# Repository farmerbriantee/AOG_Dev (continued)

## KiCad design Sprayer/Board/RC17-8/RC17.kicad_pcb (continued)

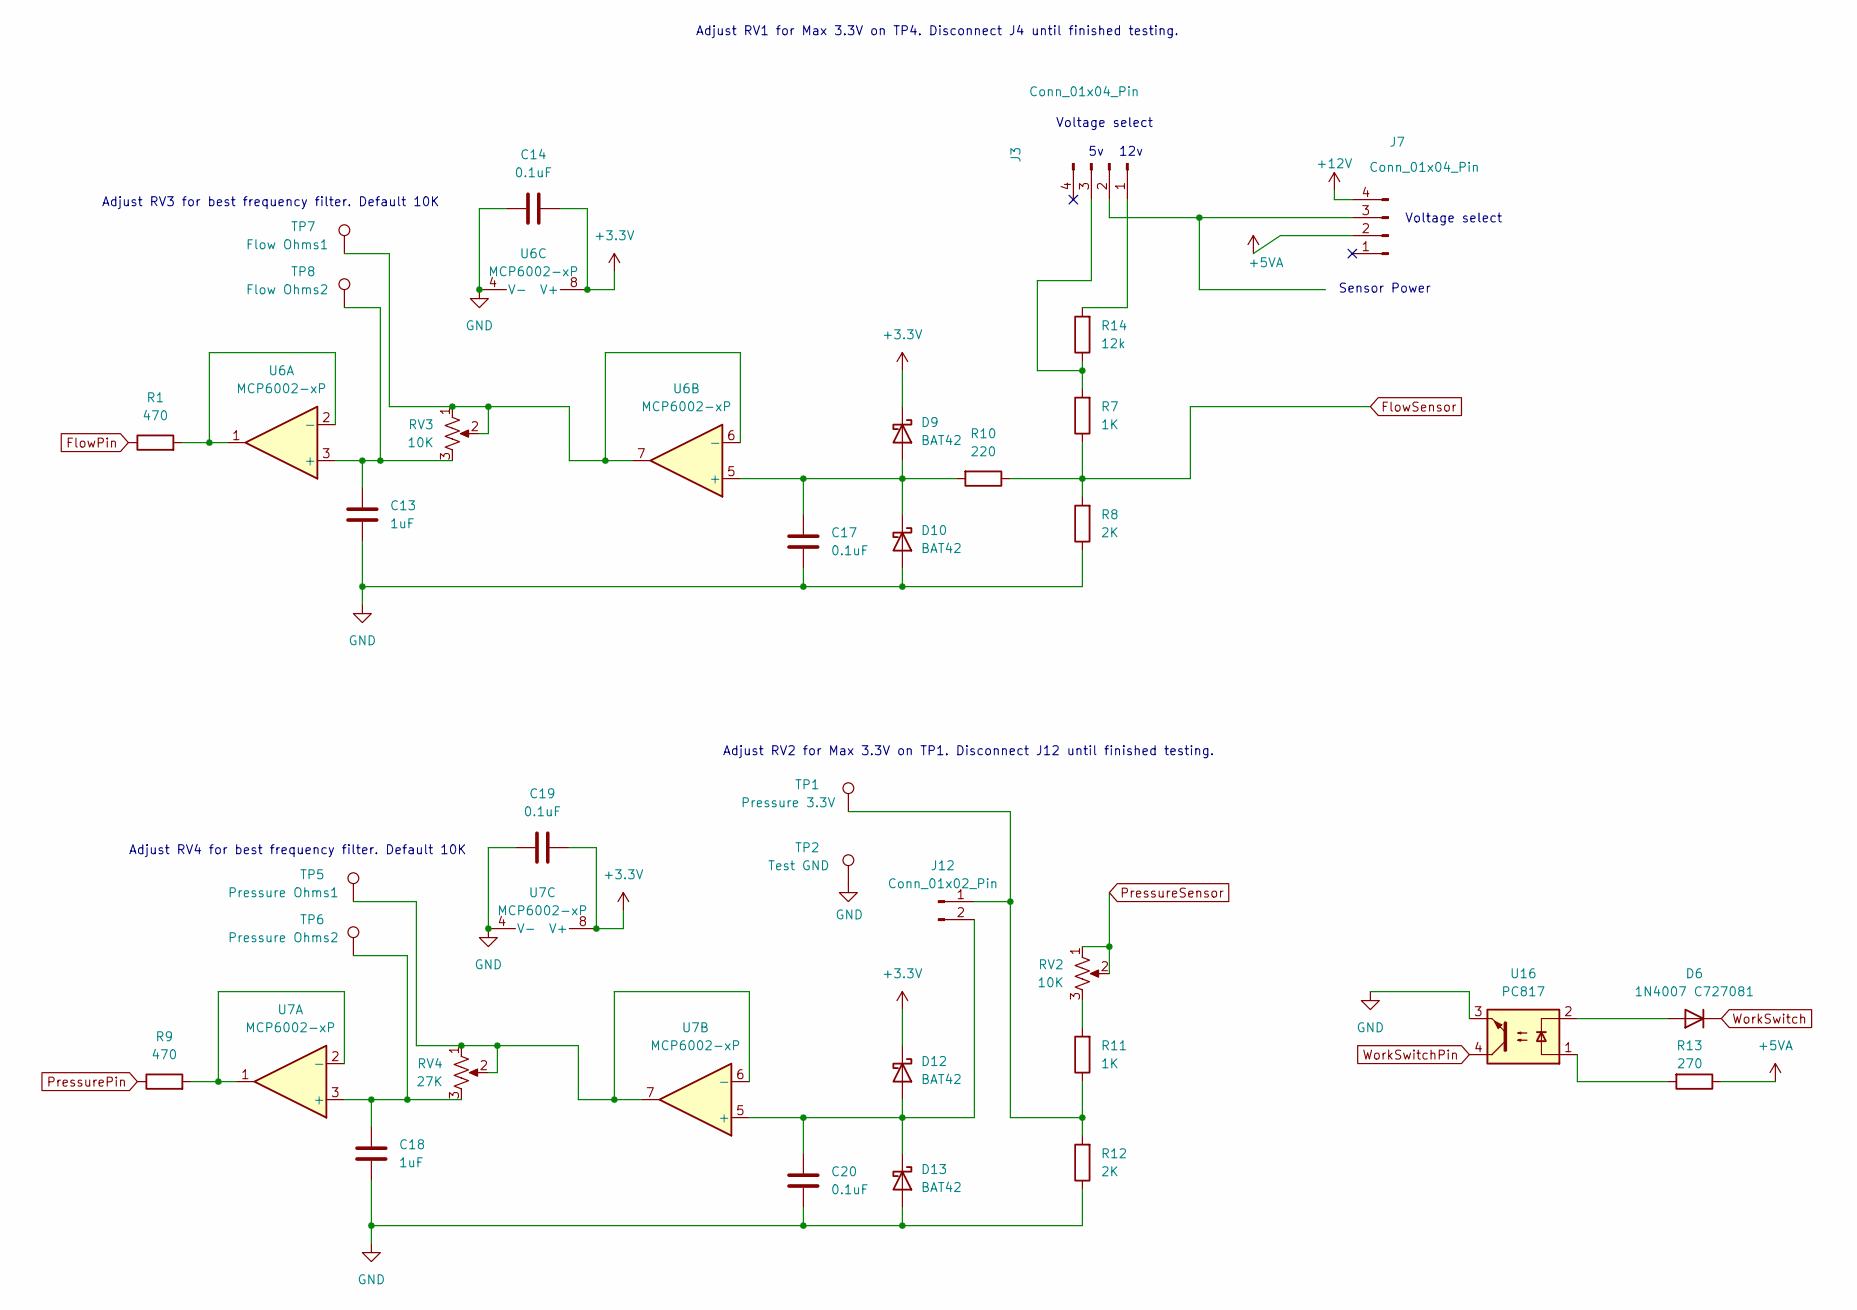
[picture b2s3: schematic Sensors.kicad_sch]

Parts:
C13, C18: 1uF; C_0805_2012Metric
C14, C17, C19, C20: 0.1uF; C_0603_1608Metric
D6: 1N4007 C727081; SMA(DO-214AC)
D9, D10, D12, D13: BAT42; D_SOD-123
J3, J7: Conn_01x04_Pin; PinHeader_1x04_P2.54mm_Vertical
J12: Conn_01x02_Pin; PinHeader_1x02_P2.54mm_Vertical
R1, R9: 470; C_0603_1608Metric
R7, R11: 1K; R_0603_1608Metric
R8, R12: 2K; R_0603_1608Metric
R10: 220; R_0603_1608Metric
R13: 270; R_0603_1608Metric
R14: 12k; R_0603_1608Metric
RV2, RV3: 10K; Potentiometer
RV4: 27K; Potentiometer
TP1: Pressure 3.3V; TestPoint_THTPad_D2.5mm_Drill1.2mm
TP2: Test GND; TestPoint_THTPad_D2.5mm_Drill1.2mm
TP5: Pressure Ohms1; TestPoint_THTPad_D2.5mm_Drill1.2mm
TP6: Pressure Ohms2; TestPoint_THTPad_D2.5mm_Drill1.2mm
TP7: Flow Ohms1; TestPoint_THTPad_D2.5mm_Drill1.2mm
TP8: Flow Ohms2; TestPoint_THTPad_D2.5mm_Drill1.2mm
U6, U7: MCP6002-xP; SOIC127P600X175-8N
U16: PC817; SMD-4_4.6x7.62mm_P2.54mm

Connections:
+3.3V: C14.2, C19.2, D9.1 (K), D12.1 (K), U6.8 (V+), U7.8 (V+); also elsewhere on the board
+5VA: J3.4, J7.2, R13.1; also elsewhere on the board
FlowPin: R1.1; also elsewhere on the board
FlowSensor: J3.2, J7.3; also elsewhere on the board
GND: C13.2, C14.1, C17.2, C18.2, C19.1, C20.2, D10.2 (A), D13.2 (A), R8.1, R12.1, TP2.1, U6.4 (V-), U7.4 (V-), U16.3; also elsewhere on the board
unnamed: D6.2 (A), U16.2
unnamed 16: C17.1, D9.2 (A), D10.1 (K), R10.2, U6.5 (+); also elsewhere on the board
unnamed: C20.1, D12.2 (A), D13.1 (K), J12.2, U7.5 (+)
unnamed 21: J3.1, R7.1, R8.2, R10.1, R14.2; also elsewhere on the board
unnamed: J12.1, R11.1, R12.2, TP1.1
unnamed: R11.2, RV2.3
unnamed: R13.2, U16.1
unnamed: C13.1, RV3.3, TP8.1, U6.3 (+)
unnamed: R1.2, U6.1, U6.2 (-)
unnamed: RV3.1, RV3.2, TP7.1, U6.6 (-), U6.7
unnamed: C18.1, RV4.3, TP6.1, U7.3 (+)
unnamed: R9.2, U7.1, U7.2 (-)
unnamed: RV4.1, RV4.2, TP5.1, U7.6 (-), U7.7
PressurePin: R9.1; also elsewhere on the board
PressureSensor: RV2.1, RV2.2; also elsewhere on the board
WorkSwitch: D6.1 (K); also elsewhere on the board
WorkSwitchPin: U16.4; also elsewhere on the board

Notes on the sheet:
Voltage select
12v
Adjust RV1 for Max 3.3V on TP4. Disconnect J4 until finished testing.
Adjust RV3 for best frequency filter. Default 10K
Adjust RV2 for Max 3.3V on TP1. Disconnect J12 until finished testing.
Sensor Power
Adjust RV4 for best frequency filter. Default 10K

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
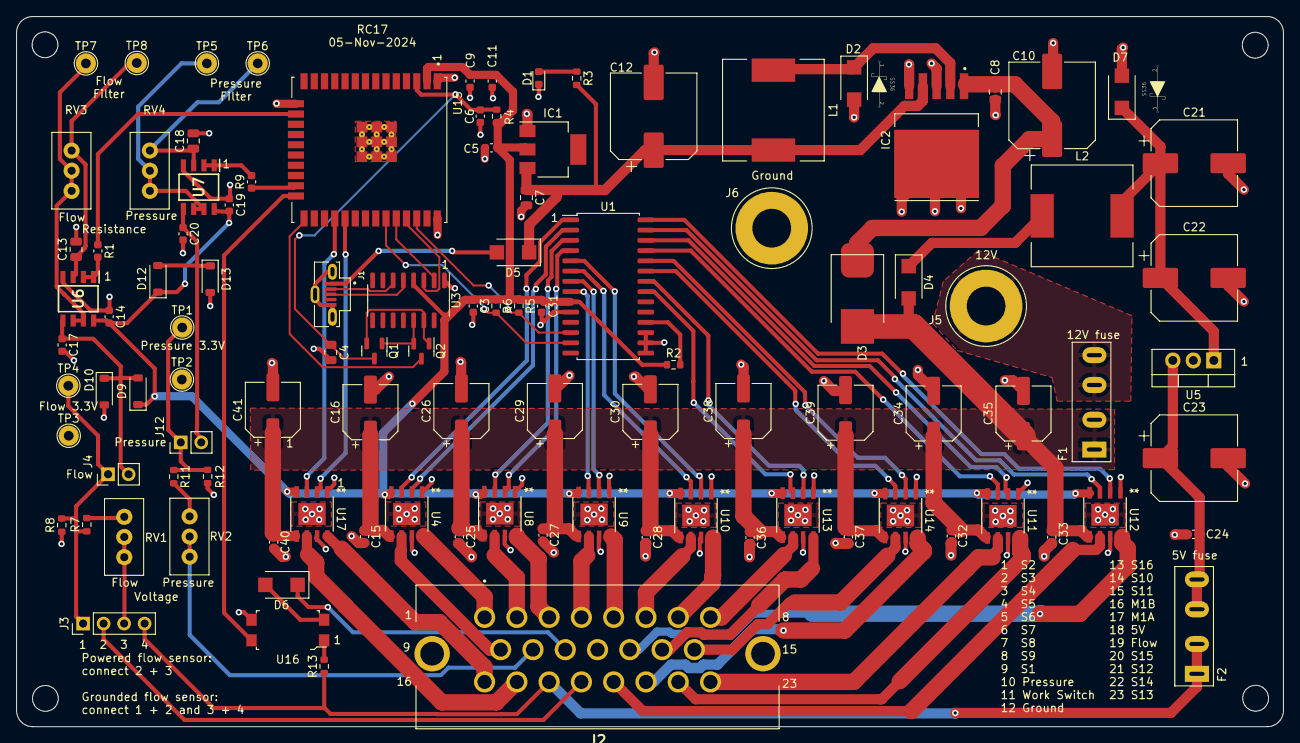
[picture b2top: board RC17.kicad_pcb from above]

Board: 2 copper layers, 157.0 x 88.0 mm, 111 parts (0 on the bottom side), 81 nets.

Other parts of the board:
 : MountingHole_3.2mm_M3
 #2,  #6: SS36 descriptor
 #3,  #4,  #5: MountingHole_3.2mm_M3
J4: Conn_01x02_Pin; PinHeader_1x02_P2.54mm_Vertical
RV1: 10K; Potentiometer
TP3: Test GND; TestPoint_THTPad_D2.5mm_Drill1.2mm
TP4: Flow 3.3V; TestPoint_THTPad_D2.5mm_Drill1.2mm

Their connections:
GND: TP3.1; also elsewhere on the board
unnamed 16: J4.2; also elsewhere on the board
unnamed 21: J4.1, TP4.1; also elsewhere on the board

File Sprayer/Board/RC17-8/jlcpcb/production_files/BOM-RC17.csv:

Comment,Designator,Footprint,LCSC
27K,RV4,Potentiometer,C118932
10K,"RV1,RV2,RV3",Potentiometer,C118954
0.1uF,"C14,C15,C17,C19,C20,C24,C25,C27,C28,C3,C31,C32,C33,C36,C37,C40,C6,C9",C_0603_1608Metric,C14663
10uF,C7,C_0805_2012Metric,C15850
S10MC,D3,D_SMC_larger_pads,C169472
500,R3,R_0603_1608Metric,C22808
270,R13,R_0603_1608Metric,C22966
2K,"R12,R8",R_0603_1608Metric,C22975
470,"R1,R9",C_0603_1608Metric,C23179
BSS138,"Q1,Q2",SOT-23,C255592
10K,"R2,R4",R_0603_1608Metric,C25804
Conn_01x04_Pin,J3,PinHeader_1x04_P2.54mm_Vertical,C2691448
1uF,"C13,C18,C4,C8",C_0805_2012Metric,C28323
47uF,"C16,C26,C29,C30,C34,C35,C38,C39,C41",CP_Elec_6.3x5.4,C2836440
SS36,"D2,D7",SMA(DO-214AC),C2903825
1K,"R11,R7",R_0603_1608Metric,C2907113
330uF,C12,CP_Elec_10x10.5,C3032175
470uF,"C10,C21,C22,C23",CP_Elec_10x10.5,C310845
776087-1-776087-1,J2,7760871,C378893
2.2K,"R5,R6",R_0603_1608Metric,C4190
MCP23017_SO,U1,SOIC-28W_7.5x17.9mm_P1.27mm,C47023
Conn_01x02_Pin,"J12,J4",PinHeader_1x02_P2.54mm_Vertical,C492401
C492610,"F1,F2",Fuse_Holder_C492610,C492610
DRV8251,"U10,U11,U12,U13,U14,U17,U4,U8,U9",DRV8251ADDR,C5218844
LM7805_TO220,U5,TO-220-3_Vertical,C5444281
BAT42,"D10,D12,D13,D9",D_SOD-123,C5805639
105133-0011,J1,MOLEX_105133-0011,C586226
22uF,"C11,C5",C_0603_1608Metric,C59461
PC817,U16,SMD-4_4.6x7.62mm_P2.54mm,C66405
ESP32-WROOM-32U,U15,XCVR_ESP32-WROOM-32U,C701344
1N4007   C727081,"D4,D5,D6",SMA(DO-214AC),C727081
MCP6002-xP,"U6,U7",SOIC127P600X175-8N,C7377
XL2596,IC2,TO263-5L,C74190
LED,D1,LED_0603_1608Metric,C84263
CH340C,U3,SOIC-16_3.9x9.9mm_P1.27mm,C84681
AZ1117,IC1,SOT-223,C92102
SMDRI127-330MT,"L1,L2",TMPA1265SP-101MN-D,C9400
Test GND,TP3,TestPoint_THTPad_D2.5mm_Drill1.2mm,
Pressure Ohms2,TP6,TestPoint_THTPad_D2.5mm_Drill1.2mm,
12V ,J5,PowerPin,
Flow Ohms2,TP8,TestPoint_THTPad_D2.5mm_Drill1.2mm,
Flow Ohms1,TP7,TestPoint_THTPad_D2.5mm_Drill1.2mm,
Pressure Ohms1,TP5,TestPoint_THTPad_D2.5mm_Drill1.2mm,
Ground,J6,PowerPin,
Pressure 3.3V,TP1,TestPoint_THTPad_D2.5mm_Drill1.2mm,
Test GND,TP2,TestPoint_THTPad_D2.5mm_Drill1.2mm,
Flow 3.3V,TP4,TestPoint_THTPad_D2.5mm_Drill1.2mm,

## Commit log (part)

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2025-02-10 Pivot heading averages
2025-02-10 Set ports to 18888, 19999. Clean up App.configs
2025-02-10 Start the jobs menu
2025-02-11 jobnew btn problem
2025-02-11 New and resume Job - basic working
2025-02-11 New and resume, multi resume for jobs
2025-02-12 Fix up Fields Form for Jobs
2025-02-12 Start double file picker
2025-02-12 Multi Open File Field and Job
2025-02-12 Circles of Pain from all the choices you can make opening and closing and resuming.
2025-02-13 Tracks to Tracklines naming oops in FormExisting
2025-02-13 Rearrange Field menu
2025-02-13 Wire up Delete btns on Field and Job picker
2025-02-13 File Picker - make functions for duplicate code
2025-02-13 ShowFields
2025-02-13 ListViewItemComparer
2025-02-13 moved ListViewItemSorter to ExtensionMethods
2025-02-13 moved patchList from CPatches to FormGPS
2025-02-14 ISOXML back on field menu
2025-02-14 Fix iso event call
2025-02-14 Clean up FormField
2025-02-14 list view sorter added to filePicker
2025-02-14 Sort added to OpenJob Picker
2025-02-14 Clean up FormFilePicker
2025-02-14 Field and Job open and new
2025-02-14 Remove job elements from KML, ISOXML andFix delete sections
2025-02-14 Jobs to open jb in picker
2025-02-15 File Validation JobNew Form
2025-02-15 oglZoom bleeding on menu
2025-02-15 Move compass
2025-02-15 FormFieldOpen Cleanup and disable buttons when no item is selected
2025-02-15 .editorConfig
2025-02-15 Field Start pos and name to opening
2025-02-16 Serbian added
2025-02-16 enable use Field once field is selected
2025-02-16 Contour button fix
2025-02-17 CSV Languages
2025-02-17 Language Keys and Values for FormGPS
2025-02-17 Language Menu change
2025-02-17 change GUI to ggStr
2025-02-17 clean up ResX
2025-02-17 gStr to ggStr for class L:ang
2025-02-18 xlsx import and language build
2025-02-18 Config Form culture labels
2025-02-18 Config and Steer label widths and translations
2025-02-18 FileSaveBoundary only when you actualy change something
2025-02-18 CalculateSectionPatchesMinMax already done in oglZoom_Paint
2025-02-18 remove csv and old xls
2025-02-18 bndSelect instead of 0
2025-02-18 tabUTurn_Leave only reset when changed
2025-02-18 remove csv from project
2025-02-19 Fix culture in BndTool
2025-02-19 Clean up translation.xls
2025-02-23 removed AppData settings
2025-02-23 NumericUpDown cleanup2
2025-02-23 NumericUpDown cleanup3
2025-02-23 double values
2025-02-24 static unit conversion
2025-02-24 use static units
2025-02-24 use mode inside NumericUpDown
2025-02-24 Font based on height
2025-02-24 fix nudZone's
2025-02-27 CNMEA cleanup
2025-02-27 Update AgIO to dual
2025-02-27 fix numeric font size
2025-02-27 Finalize comms between tool and gps, Scan and Hello
2025-02-28 remove isMetric
2025-02-28 distanceFromCurrentLine in meters
2025-02-28 distanceFromCurrentLine in meters2
2025-02-28 rename agone to AgIO
2025-02-28 Sort Settings
2025-03-01 use pivotAxlePos instead of fix
2025-03-01 cleanup fix-fix calculation (needs testing in field)
2025-03-01 button should work when revers is off
2025-03-01 Revert "Fix Antenna dots"
    This reverts commit 76b627b59456f8a2280241dca5fc5241301b7237.
2025-03-01 toolpos for oglBack not pivot
2025-03-02 larger bounding box for section culling
2025-03-02 changed sim so its rotation around a center
2025-03-02 FileOpenField cleanup
2025-03-02 removed unnecessary SetZoom calls
2025-03-02 cleanup variables
2025-03-02 simplify PanelsAndOGLSize & CheckColorFor255
2025-03-02 Contour and YouTurn steerangle calculations to guidance class
2025-03-03 Separate Vehicle, Tool & Interface
2025-03-03 Save & load for ToolSettings
2025-03-03 set lat&lon on sim reset
2025-03-03 RepeatButton
2025-03-03 removed References
2025-03-03 fix Settings
2025-03-03 automatic changed designer code
2025-03-03 interface to user
2025-03-03 Config form to vehicle/tool outline
2025-03-03 Resort and Rename settings
2025-03-03 Rename User settings moved from vehicle
2025-03-03 Endless renaming sheesh
2025-03-04 Remove display settings to variable doubling
2025-03-04 And more settings to props removed
2025-03-04 cleanup customColors & buttonOrder & swapDayNight
2025-03-04 FormConfig cleanup and fix tab Enter/Leave
2025-03-04 use settings directly
2025-03-04 use settings directly less reloading of all settings
2025-03-04 Settings Save to Profile. Not quite there
2025-03-04 Fix Save and Load
2025-03-04 Sort and group AgIO settings
2025-03-05 serial double settings
2025-03-05 Clean up settings, final double deletes
2025-03-05 Cam Pitch and Zoom doubles
2025-03-05 double settings
2025-03-05 Tool Setting duplicates
2025-03-05 opengl -> lost and isFirstHeadingSet move to Ortho drawing
2025-03-05 simplify btnSection and btnZone buttons
2025-03-06 fix zone button
2025-03-06 Youturn
2025-03-07 PerformClick to function call for autosteer and youturn
2025-03-07 more room for youTurnPhases
2025-03-07 GPS Out Class
2025-03-07 wrong branch, oops
2025-03-08 GPSOut settings
2025-03-08 Fix up main gui
2025-03-08 Traffic to GPSOut controls red green for button
2025-03-09 Writeline to Write
2025-03-09 Graphics and positioning for Win 11 and win 10
2025-03-09 proper byte counting
2025-03-09 Fix keyboard from sizing
2025-03-10 Add labels for load save new
2025-03-10 BackgroundWorker with skip send if still sending
2025-03-10 Remove awkward rtcm messages
2025-03-10 survive buffer overflow
2025-03-11 Fixed Distance Lookahead
2025-03-11 fix sim reverse
2025-03-11 sim heading after reset
2025-03-12 lengthen Track if close to ends
2025-03-12 fix Uturn gets longer too
2025-03-12 time based
2025-03-12 Vehicle/Tool loading and saving made easier, updates labels. Remove Ask on Load. No close after loading vehicle
2025-03-13 Add GSA and ZDA to GPSOut
2025-03-13 catch e removed
2025-03-14 Set nuds to Small
2025-03-15 Redo summary page of config
2025-03-15 Convert To AOG
2025-03-15 update ignore
2025-03-15 AgOpenGPS -> AOG
2025-03-16 First Screen, Remove any Default XML files or saving
2025-03-16 update labels functions
2025-03-17 PGN233 Tool Data fixed
2025-03-18 Dubins removed, Nozzle and section build added, Nud formatting fixed
2025-03-18 Fix up nozz display panel
2025-03-18 Modsim btn to run from AgIO
2025-03-18 reset U-turn when guidance line changes
2025-03-18 new vec2 from vec3
2025-03-19 local values
2025-03-19 if enabled it turns off U-turn when line changes
2025-03-19 fix track loading & U-turn
2025-03-24 Change settings and field icons to look different
2025-03-27 TM171 code added
2025-03-27 update spray board
2025-03-29 Refactor duplicate functions into extension methods
2025-04-01 untouched v4.1 firmware
2025-04-01 reset v4.1 firmware
2025-04-01 Add changes
2025-04-02 board gerber
2025-04-03 Clean up and speed up 4.1 firmware
2025-04-03 while back to if
2025-04-05 ToolSteer Firmware made
2025-04-05 Clean up files and dirs
2025-04-06 Add NanoSpray
2025-04-07 fix esp pid
2025-04-08 Spray ESP32 code fixes
2025-04-08 Nozzle config settings fixed
2025-04-08 local reference
2025-04-08 unnecessary track design Clear
2025-04-08 combined BuildTracks and QuickAB readonly List<CTrk>
2025-04-09 Add NozzESP
2025-04-09 Nozzle fixes
2025-04-10 Noz config Hz added
2025-04-10 126 to 226 for steer module
2025-04-10 Nozzle mods and Firmware update for limits
2025-04-10 uturn buttons visible more
2025-04-11 remove some files
2025-04-11 Change network for ESP
2025-04-11 Change network back to 1.1
2025-04-11 isSteer sent for pgn
2025-04-12 fixes in headache and handline forms
2025-04-12 Revert "uturn buttons visible more"
    This reverts commit 8490d8eeedc892067f2190cbf0d687ce638eec13.
2025-04-12 Antenna Height and Offset settings in steer form
2025-04-13 Add roll correction and Fix slide/steer roll effect
2025-04-13 toolDual hex
2025-04-13 Add tool antenna offset compensation.
2025-04-13 fix DrawPolygon for LineStrips
2025-04-14 AP Mode ESP32
2025-04-14 fix oglBack drawing and Section_Widths not loading correctly
2025-04-15 Currently being drawn patches to BBuffer
2025-04-15 update Nozzle labels
2025-04-15 Fix section width nuds
2025-04-15 fix ab line extension
2025-04-16 Minor refactoring, make the PGNs more readable
2025-04-17 fix offset u-turn & offset saving
2025-04-17 NozzNano Sln
2025-04-17 More data on Nozz config screen
2025-04-18 Clean up nozzle config
2025-04-19 Add IMU TM171 serial
2025-04-21 Metering and Flow selection, Kp added
2025-04-21 USe Pow for metering gain
2025-04-21 Arrange Nozzle Confiog
2025-04-21 Separate metering and Flow nuds
2025-04-22 Section Lights color correct for day night
2025-04-23 NozzESP Metering gain function simplify
2025-04-23 Invert roll - button did nothing. Add event.
2025-04-26 add metering to NozzNano
2025-04-27 toggle contour lock state on autosteerbtn press.
2025-04-27 Fix AgIO keyobard for culture
2025-04-27 roll tracking
2025-04-28 IMU set to 6 bytes for speed
2025-04-29 Add Edge Finding ABLine
2025-04-30 Fix the ISOXML
2025-05-01 add vtg back in
2025-05-01 Remove jump fix test thingy
2025-05-03 antenna offset to +-2m
2025-05-04 fix U-turn math problem
2025-05-04 Add back in gpsPts
2025-05-04 Allow send to serial and udp RTCM
2025-05-04 Allow udp and serial rtcm
2025-05-05 U-turn failed when a-b segment is created outside the boundary
2025-05-07 Remove smoothing.
2025-05-08 remove extra points in AB lines
2025-05-12 DebuggerDisplay
2025-05-12 U-turn use right segment
2025-05-13 Add Create heading for ABDraw
2025-05-13 Add heading to EdgeAB
2025-05-14 Try catch around DrawPolygon NozzNano updates
2025-05-14 Add GPS Correction line setting
2025-05-14 Fix the short line issue ABDraw
2025-05-14 vec3 to vec2
2025-05-14 cleanup vec3.cs
2025-05-15 removed Math.Round for defaultSectionWidth
2025-05-15 section array to list with max 256 sections
2025-05-15 Redo BndTool Gui
2025-05-17 cleanup some code
2025-05-17 isRemoteSectionControl
2025-05-17 imu and bnd Tool changes
2025-05-19 Create Tool Steer Settings
2025-05-20 Build tool steer form for settings
2025-05-20 Extend endpoints for AB Lines in ABDraw
2025-05-23 Init Classes and uploader
2025-05-23 Make FileSaveEverything Async
2025-05-23 Store as Polygon
2025-05-23 Add Images
2025-05-23 async task if for Closing AOG with AgShareUpload
2025-05-23 add Activate button formAgShareSettings
2025-05-23 Upload Methods added
2025-05-23 small fix when we close the field
2025-05-23 New Closing Method to match upload with AgShare
2025-05-25 fix resource.resx AgShare
2025-05-25 inconsistent AgShare settings
2025-05-25 Cleanup AgShare, add Linklabel, Keyboard link, PasteClipboardBtn
2025-05-25 Upload Outer and Innerboundaries
2025-05-25 clean
2025-05-25 fix missing flag and Add Innerboundaries to Upload Method for AgShare (#66)
    * set isAgShareUploader to false when done
    * Upload Outer and Innerboundaries
    * clean
2025-05-27 initial stuff for Downloader
2025-05-29 section lbl's to section count instead of zones
2025-05-29 use remoteSectionControl bool instead of settings
2025-05-29 AgShare Download options done
2025-06-07 better split in upload download
2025-06-08 Cleanup AgShare Classes
2025-06-20 fix DoRemoteSwitches not changing buttons
2025-06-22 initial av
2025-06-22 Fix AgIO
2025-06-23 Tool antenna offser from 2m to 5m
2025-06-24 Remove tool settings
2025-06-24 remove tool steer from steer form
2025-06-25 UDP fixes - again
2025-07-09 attempt to make sense of what all is different between AOG and AgOpenGPS
2025-07-09 fix lateral and manual uturn bugs Lateral and manual uturn button clicks were still being registered, and moving the line over and/or drawing uturn lines even when the icons weren't being shown. This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
2025-07-09 Implements visual save progress indicator
    Replaces the timed message box with a new FormSaving to visually display the progress of saving field data and settings during shutdown.
    This new form displays a progress bar and a list of steps, including saving field parameters, uploading to AgShare (if enabled), saving the field locally, and saving settings. It also adds a final me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
    This provides a more informative and user-friendly experience during the shutdown process.
2025-07-12 add actual
2025-07-18 Add AV Steer
2025-07-30 Export field KML
2025-08-08 AgShare create snapshot on close dont upload anything when sharing is off
2025-08-16 av test drive
2025-09-02 change line update from 3 to 2 seconds
